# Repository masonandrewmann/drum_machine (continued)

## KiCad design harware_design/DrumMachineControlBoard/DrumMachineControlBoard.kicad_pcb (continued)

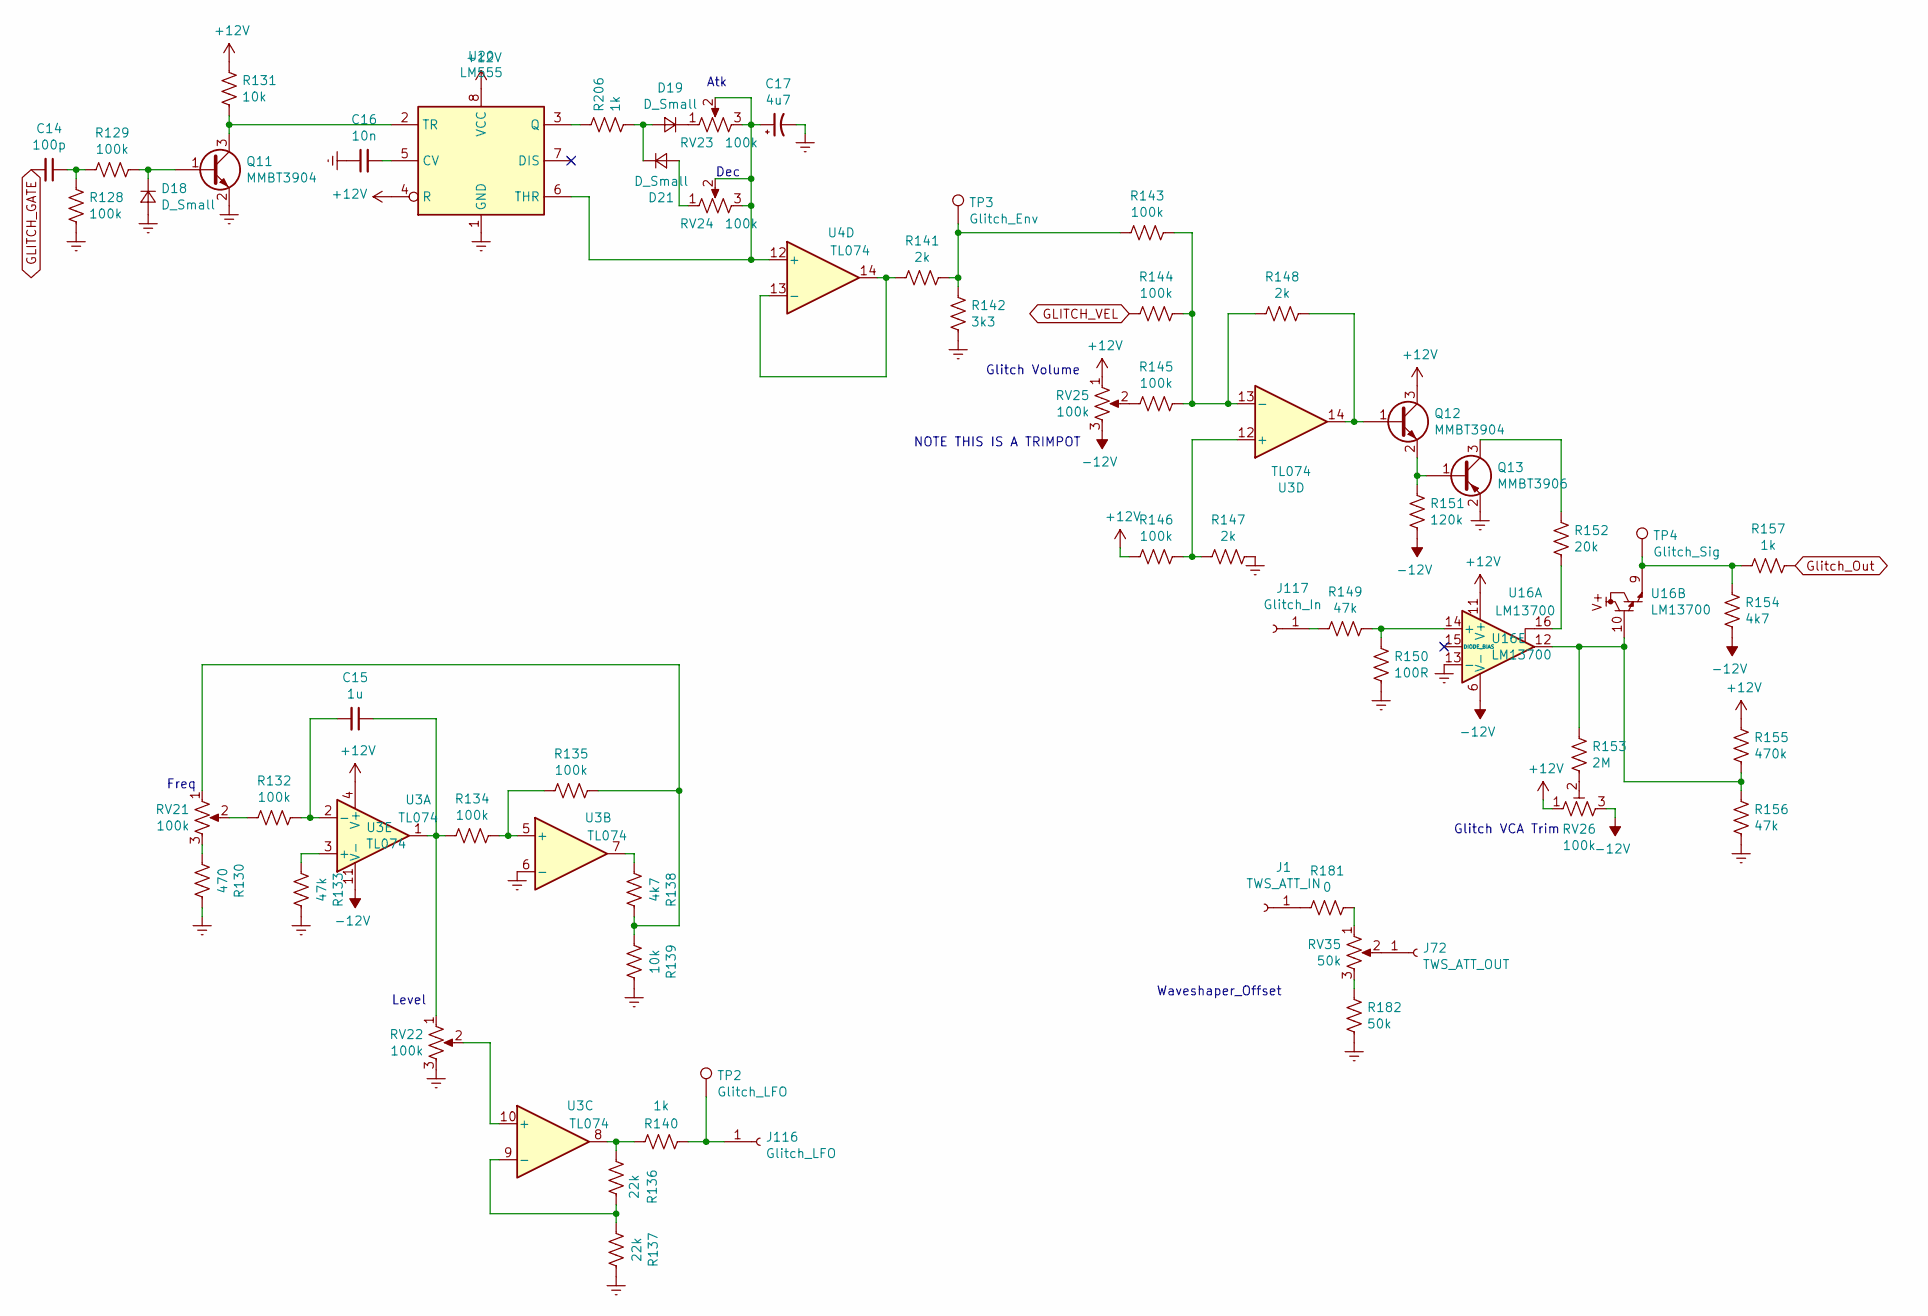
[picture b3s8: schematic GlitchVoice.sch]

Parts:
C14: 100p; C_0603_1608Metric_Pad1.05x0.95mm_HandSolder
C15: 1u; CP_Elec_4x4.5
C16: 10n; C_0603_1608Metric_Pad1.05x0.95mm_HandSolder
C17: 4u7; CP_Elec_4x4.5
D18, D19, D21: D_Small; D_SOD-123
J1: TWS_ATT_IN; SolderWirePad_1x01_Drill1mm
J72: TWS_ATT_OUT; SolderWirePad_1x01_Drill1mm
J116: Glitch_LFO; SolderWirePad_1x01_Drill1mm
J117: Glitch_In; SolderWirePad_1x01_Drill1mm
Q11, Q12: MMBT3904; SOT-23
Q13: MMBT3906; SOT-23
R128, R129, R132, R134, R135, R143, R144, R145, R146: 100k; R_0603_1608Metric_Pad1.05x0.95mm_HandSolder
R130: 470; R_0603_1608Metric_Pad1.05x0.95mm_HandSolder
R131, R139: 10k; R_0603_1608Metric_Pad1.05x0.95mm_HandSolder
R133, R149, R156: 47k; R_0603_1608Metric_Pad1.05x0.95mm_HandSolder
R136, R137: 22k; R_0603_1608Metric_Pad1.05x0.95mm_HandSolder
R138, R154: 4k7; R_0603_1608Metric_Pad1.05x0.95mm_HandSolder
R140, R157, R206: 1k; R_0603_1608Metric_Pad1.05x0.95mm_HandSolder
R141, R147, R148: 2k; R_0603_1608Metric_Pad1.05x0.95mm_HandSolder
R142: 3k3; R_0603_1608Metric_Pad1.05x0.95mm_HandSolder
R150: 100R; R_0603_1608Metric_Pad1.05x0.95mm_HandSolder
R151: 120k; R_0603_1608Metric_Pad1.05x0.95mm_HandSolder
R152: 20k; R_0603_1608Metric_Pad1.05x0.95mm_HandSolder
R153: 2M; R_0603_1608Metric_Pad1.05x0.95mm_HandSolder
R155: 470k; R_0603_1608Metric_Pad1.05x0.95mm_HandSolder
R181: 0; R_0603_1608Metric_Pad1.05x0.95mm_HandSolder
R182: 50k; R_0603_1608Metric_Pad1.05x0.95mm_HandSolder
RV21, RV22, RV23, RV24: 100k; masonsPotentiometer_Alpha_RD901F-40-00D_Single_Vertical
RV25, RV26: 100k; Potentiometer_Runtron_RM-065_Vertical
RV35: 50k; masonsPotentiometer_Alpha_RD901F-40-00D_Single_Vertical
TP2: Glitch_LFO; TestPoint_Loop_D2.50mm_Drill1.0mm
TP3: Glitch_Env; TestPoint_Loop_D2.50mm_Drill1.0mm
TP4: Glitch_Sig; TestPoint_Loop_D2.50mm_Drill1.0mm
U3, U4: TL074; SOIC-14_3.9x8.7mm_P1.27mm
U16: LM13700; SOIC-16_3.9x9.9mm_P1.27mm
U20: LM555; DIP-8_W7.62mm_Socket

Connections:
-12V: R151.2, R154.2, RV25.3, RV26.3, U3.11 (V-), U16.6 (V-); also elsewhere on the board
GLITCH_GATE: C14.2; also elsewhere on the board
GLITCH_VEL: R144.2; also elsewhere on the board
Glitch_Out: R157.1; also elsewhere on the board
unnamed: C14.1, R128.1, R129.2
unnamed: C15.1, R134.2, RV22.1, U3.1
unnamed: C15.2, R132.1, U3.2 (-)
unnamed: C16.2, U20.5 (CV)
unnamed: C17.1, RV23.2, RV23.3, RV24.2, RV24.3, U4.12 (+), U20.6 (THR)
unnamed: D18.1 (K), Q11.1 (B), R129.1
unnamed: D19.1 (K), RV23.1
unnamed: D19.2 (A), D21.1 (K), R206.1
unnamed: D21.2 (A), RV24.1
unnamed: J1.1, R181.2
unnamed: J72.1, RV35.2
unnamed: J116.1, R140.2, TP2.1
unnamed: J117.1, R149.2
unnamed: Q11.3 (C), R131.1, U20.2 (TR)
unnamed: Q12.1 (B), R148.1, U3.14
unnamed: Q12.2 (E), Q13.1 (B), R151.1
unnamed: Q13.3 (C), R152.1
unnamed: R130.2, RV21.3
unnamed: R132.2, RV21.2
unnamed: R133.2, U3.3 (+)
unnamed: R134.1, R135.2, U3.5 (+)
unnamed: R135.1, R138.1, R139.2, RV21.1
unnamed: R136.1, R137.2, U3.9 (-)
unnamed: R136.2, R140.1, U3.8
unnamed: R138.2, U3.7
unnamed: R141.1, U4.13 (-), U4.14
unnamed: R141.2, R142.1, R143.2, TP3.1
unnamed: R143.1, R144.1, R145.1, R148.2, U3.13 (-)
unnamed: R145.2, RV25.2
unnamed: R146.1, R147.2, U3.12 (+)
unnamed: R149.1, R150.1, U16.14 (+)
unnamed: R152.2, U16.16
unnamed: R153.1, R155.2, R156.1, U16.10, U16.12
unnamed: R153.2, RV26.2
unnamed: R154.1, R157.2, TP4.1, U16.9
unnamed: R181.1, RV35.1
unnamed: R182.2, RV35.3
unnamed: R206.2, U20.3 (Q)
unnamed: RV22.2, U3.10 (+)

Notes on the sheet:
Glitch Volume
Glitch VCA Trim
Level
Freq
Atk
Dec
NOTE THIS IS A TRIMPOT
Waveshaper_Offset

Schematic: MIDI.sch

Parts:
D20: 1N4148; D_SOD-123
J11: MIDI IN; DIN5_MIDI
J12: MIDI THRU; DIN5_MIDI
J13: MIDI OUT; DIN5_MIDI
R158, R159, R160, R161: 220; R_0805_2012Metric_Pad1.15x1.40mm_HandSolder
R162: 1k; R_0805_2012Metric_Pad1.15x1.40mm_HandSolder
U21: 74LS04; SOIC-14_3.9x8.7mm_P1.27mm
U22: PC817; DIP-4_W7.62mm

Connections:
+5V: R159.1, R162.2, U21.14 (VCC); also elsewhere on the board
MIDI_IN: R162.1, U21.5, U22.4; also elsewhere on the board
MIDI_OUT: U21.1; also elsewhere on the board
unnamed: D20.1 (K), R160.1, U22.1
unnamed: D20.2 (A), J11.5, U22.2
unnamed: J11.4, R160.2
unnamed 170: J12.4; also elsewhere on the board
unnamed: J12.5, R161.2
unnamed: J13.4, R159.2
unnamed: J13.5, R158.2
unnamed: R158.1, U21.4
unnamed: R161.1, U21.8
unnamed: U21.2, U21.3
unnamed: U21.6, U21.9

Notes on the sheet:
TRIPLE CHECK PINOUT!!!
IDK if any of these circuits work lmao
ALSO LOGIC LEVVELS!
Its not pulling down enough with this resistor
but does when i short it
works better with 220ohm pullup

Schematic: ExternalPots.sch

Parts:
J17: out1W; SolderWirePad_1x01_Drill1mm
J18: env3; SolderWirePad_1x01_Drill1mm
J19: lvl1; SolderWirePad_1x01_Drill1mm
J20: noiseA; SolderWirePad_1x01_Drill1mm
J24: freqA; SolderWirePad_1x01_Drill1mm
J25: env2; SolderWirePad_1x01_Drill1mm
J26: lvl3W; SolderWirePad_1x01_Drill1mm
J27: noise/shimA; SolderWirePad_1x01_Drill1mm
J29: CYNCM_A; SolderWirePad_1x01_Drill1mm
J30: HP_A; SolderWirePad_1x01_Drill1mm
J31: out3; SolderWirePad_1x01_Drill1mm
J32: env1; SolderWirePad_1x01_Drill1mm
J34: shimA; SolderWirePad_1x01_Drill1mm
J35: BP_A; SolderWirePad_1x01_Drill1mm
J36: LP_A; SolderWirePad_1x01_Drill1mm
J37: CYNCM_B; SolderWirePad_1x01_Drill1mm
J38: res1A; SolderWirePad_1x01_Drill1mm
J39: dec1A; SolderWirePad_1x01_Drill1mm
J41: HP_B; SolderWirePad_1x01_Drill1mm
J42: BP_B; SolderWirePad_1x01_Drill1mm
J43: LP_B; SolderWirePad_1x01_Drill1mm
J44: res23A; SolderWirePad_1x01_Drill1mm
J45: dec23A; SolderWirePad_1x01_Drill1mm
J57: Env_1B; SolderWirePad_1x01_Drill1mm
J59: noiseB; SolderWirePad_1x01_Drill1mm
J63: freqB; SolderWirePad_1x01_Drill1mm
J64: Env_2B; SolderWirePad_1x01_Drill1mm
J66: noise/shimB; SolderWirePad_1x01_Drill1mm
J71: Env_3B; SolderWirePad_1x01_Drill1mm
J73: shimB; SolderWirePad_1x01_Drill1mm
J77: res1B; SolderWirePad_1x01_Drill1mm
J78: dec1B; SolderWirePad_1x01_Drill1mm
J83: res23B; SolderWirePad_1x01_Drill1mm
J84: dec23B; SolderWirePad_1x01_Drill1mm
J92: atk1W; SolderWirePad_1x01_Drill1mm
J93: tune; SolderWirePad_1x01_Drill1mm
J94: dist1W; SolderWirePad_1x01_Drill1mm
J95: snap1; SolderWirePad_1x01_Drill1mm
J96: Tone1; SolderWirePad_1x01_Drill1mm
J101: Tone2; SolderWirePad_1x01_Drill1mm
J102: atk3; SolderWirePad_1x01_Drill1mm
J104: dist3; SolderWirePad_1x01_Drill1mm
J105: snap3w; SolderWirePad_1x01_Drill1mm
J106: Tone3; SolderWirePad_1x01_Drill1mm
J107: tune3; SolderWirePad_1x01_Drill1mm
J108: depth1; SolderWirePad_1x01_Drill1mm
J109: dec1w; SolderWirePad_1x01_Drill1mm
J110: tunew; SolderWirePad_1x01_Drill1mm
J111: depthw; SolderWirePad_1x01_Drill1mm
J113: tune1; SolderWirePad_1x01_Drill1mm
J114: depth3; SolderWirePad_1x01_Drill1mm
J115: dec3; SolderWirePad_1x01_Drill1mm
J146: AuxPot1; SolderWirePad_1x01_Drill1mm
J147, J148: AuxPot2; SolderWirePad_1x01_Drill1mm
J149: AuxPot1A; SolderWirePad_1x01_Drill1mm
J150, J151: AuxPot2A; SolderWirePad_1x01_Drill1mm
RV8, RV30, RV33, RV40, RV49, RV52, RV54, RV55, RV57, RV66: 100k; masonsPotentiometer_Alpha_RD901F-40-00D_Single_Vertical
RV14: 50k; masonsPotentiometer_Alpha_RD901F-40-00D_Single_Vertical
RV31, RV50: 25k; masonsPotentiometer_Alpha_RD901F-40-00D_Single_Vertical
RV39, RV56: 1k; masonsPotentiometer_Alpha_RD901F-40-00D_Single_Vertical
RV59: 470; Amphenol_Trimpot
RV60, RV61, RV62, RV64: 10k; masonsPotentiometer_Alpha_RD901F-40-00D_Single_Vertical
RV63: 500k; masonsPotentiometer_Alpha_RD901F-40-00D_Single_Vertical
RV65: 1M; masonsPotentiometer_Alpha_RD901F-40-00D_Single_Vertical
U26: SP3TCYNA; two-pole-switch
U27: SP3TCYNB; two-pole-switch

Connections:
-12V: RV30.1, RV49.1; also elsewhere on the board
unnamed: J17.1, RV14.1, RV14.2
unnamed: J18.1, RV31.1
unnamed: J19.1, RV8.1
unnamed: J20.1, RV33.1
unnamed: J24.1, RV30.2
unnamed: J25.1, RV31.2
unnamed: J26.1, RV8.2, RV8.3
unnamed: J27.1, RV33.2
unnamed: J29.1, U26.2
unnamed: J30.1, U26.1
unnamed: J31.1, RV14.3
unnamed: J32.1, RV31.3
unnamed: J34.1, RV33.3
unnamed: J35.1, U26.4
unnamed: J36.1, U26.6
unnamed: J37.1, U27.2
unnamed: J38.1, RV39.1
unnamed: J39.1, RV40.1
unnamed: J41.1, U27.1
unnamed: J42.1, U27.4
unnamed: J43.1, U27.6
unnamed: J44.1, RV39.2, RV39.3
unnamed: J45.1, RV40.2, RV40.3
unnamed: J57.1, RV50.1
unnamed: J59.1, RV52.1
unnamed: J63.1, RV49.2
unnamed: J64.1, RV50.2
unnamed: J66.1, RV52.2
unnamed: J71.1, RV50.3
unnamed: J73.1, RV52.3
unnamed: J77.1, RV56.1
unnamed: J78.1, RV57.1
unnamed: J83.1, RV56.2, RV56.3
unnamed: J84.1, RV57.2, RV57.3
unnamed: J92.1, RV59.1, RV59.2
unnamed: J93.1, RV60.1
unnamed: J94.1, RV61.1, RV61.2
unnamed: J95.1, RV62.1
unnamed: J96.1, RV63.1
unnamed: J101.1, RV63.2
unnamed: J102.1, RV59.3
unnamed: J104.1, RV61.3
unnamed: J105.1, RV62.2, RV62.3
unnamed: J106.1, RV63.3
unnamed: J107.1, RV64.1
unnamed: J108.1, RV65.1
unnamed: J109.1, RV66.1, RV66.2
unnamed: J110.1, RV64.2
unnamed: J111.1, RV65.2
unnamed: J113.1, RV64.3
unnamed: J114.1, RV65.3
unnamed: J115.1, RV66.3
unnamed: J146.1, RV54.1
unnamed: J147.1, RV54.2
unnamed: J148.1, RV54.3
unnamed: J149.1, RV55.1
unnamed: J150.1, RV55.2
unnamed: J151.1, RV55.3
unnamed: U26.3, U26.5
unnamed: U27.3, U27.5

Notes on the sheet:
VCF_FreqA
VCF_ResA
EnvA
DecA
Shim/NoiseA
CYNARE A
VCF_FreqB
VCF_ResB
EnvB
DecB
Shim/NoiseB
CYNARE B
Atk
Dec
TuneDep
TuneDec
Dist
Bass Drum
Snap
Tune
Tone
Snare
level

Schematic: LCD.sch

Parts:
J145: Conn_01x08_Female; PinSocket_1x08_P2.54mm_Vertical
R177: 220; R_0603_1608Metric_Pad1.05x0.95mm_HandSolder
U24: Nokia5110; Nokia5110Breakout

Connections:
+3V3: J145.3, R177.2, U24.3 (VCC); also elsewhere on the board
LCD_CS: J145.7, U24.7 (CE); also elsewhere on the board
LCD_DC: J145.6, U24.6 (DC); also elsewhere on the board
LCD_RST: J145.8, U24.8 (RST); also elsewhere on the board
MEM_MOSI: J145.5, U24.5 (DIN)
MEM_SCK: J145.4, U24.4 (CLK); also elsewhere on the board
unnamed: J145.2, R177.1, U24.2 (LIGHT)

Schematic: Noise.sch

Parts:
C30: 1u; CP_Elec_4x4.5
C36: 100n; C_0603_1608Metric_Pad1.05x0.95mm_HandSolder
C37: 10u; CP_Elec_5x5.3
J14: BD_Noise; SolderWirePad_1x01_Drill1mm
J15: Snare_Noise; SolderWirePad_1x01_Drill1mm
Q23: 2N3904; TO-92_Inline_Wide
R194: 2M; R_0603_1608Metric_Pad1.05x0.95mm_HandSolder
R195: 100k; R_0603_1608Metric_Pad1.05x0.95mm_HandSolder
R196: 4M7; R_0603_1608Metric_Pad1.05x0.95mm_HandSolder
R197, R198: 10k; R_0603_1608Metric_Pad1.05x0.95mm_HandSolder
R199, R200: 2M; R_Axial_DIN0207_L6.3mm_D2.5mm_P7.62mm_Horizontal
R207, R208: 470k; R_0603_1608Metric_Pad1.05x0.95mm_HandSolder
RV11, RV15: 100k; Potentiometer_Runtron_RM-065_Vertical
U29: TL074; SOIC-14_3.9x8.7mm_P1.27mm

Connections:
-12V: Q23.2 (B), U29.11 (V-); also elsewhere on the board
unnamed: C30.1, R207.1, R208.1
unnamed: C36.1, Q23.1 (E), R208.2
unnamed: C36.2, R194.1, U29.3 (+)
unnamed: C37.1, R195.1
unnamed: J14.1, R200.1, U29.7
unnamed: J15.1, R199.1, U29.8
unnamed: R195.2, R196.2, U29.2 (-)
unnamed: R196.1, RV11.1, RV15.1, U29.1
unnamed: R197.1, R200.2, U29.6 (-)
unnamed: R197.2, RV11.2
unnamed: R198.1, R199.2, U29.9 (-)
unnamed: R198.2, RV15.2

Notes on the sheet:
BD_Noise_LVL
Snare_Noise_LVL

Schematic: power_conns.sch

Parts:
J47: PWR_CONN; JST_XH_B5B-XH-A_1x05_P2.50mm_Vertical
J48: SNARE_PWR; JST_XH_B3B-XH-A_1x03_P2.50mm_Vertical
J49: BD_PWR; JST_XH_B3B-XH-A_1x03_P2.50mm_Vertical
J50: CYN1_PWR; JST_XH_B3B-XH-A_1x03_P2.50mm_Vertical
J51: CYN2_PWR; JST_XH_B3B-XH-A_1x03_P2.50mm_Vertical
J52: TWS_PWR; JST_XH_B3B-XH-A_1x03_P2.50mm_Vertical

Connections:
+5V: J47.2; also elsewhere on the board
-12V: J47.5, J48.3, J49.3, J50.3, J51.3, J52.3; also elsewhere on the board

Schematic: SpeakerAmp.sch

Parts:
C24: 10u; CP_Elec_4x4.5
C25: 100n; C_0805_2012Metric_Pad1.15x1.40mm_HandSolder
J16: spk_Conn; JST_XH_B2B-XH-A_1x02_P2.50mm_Vertical
R180: 10k; R_0805_2012Metric_Pad1.15x1.40mm_HandSolder
RV16: 1M; Potentiometer_Runtron_RM-065_Vertical
SW33: SW_SPDT; one-pole-switch
U28: NJM2073S; SIP-9_21.54x3mm_P2.54mm

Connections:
unnamed: C24.1, U28.9 (A-)
unnamed: C24.2, C25.1, U28.6 (B-)
unnamed: J16.1, U28.4 (B_Out)
unnamed: J16.2, U28.2 (A_Out)
unnamed: R180.2, RV16.3, U28.8 (A+)
unnamed: RV16.1, RV16.2, SW33.2 (B)

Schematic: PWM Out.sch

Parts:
C18, C19, C20, C21, C22, C23: 100n; C_0805_2012Metric_Pad1.15x1.40mm_HandSolder
J124: Kick_Vel; SolderWirePad_1x01_Drill1mm
J125: Snare_Vel; SolderWirePad_1x01_Drill1mm
J126: CYN1_Vel; SolderWirePad_1x01_Drill1mm
J127: CYN2_Vel; SolderWirePad_1x01_Drill1mm
R163, R164, R165, R166, R171, R172: 10k; R_0805_2012Metric_Pad1.15x1.40mm_HandSolder
R167, R168, R169, R170, R173, R174: 4k7; R_0805_2012Metric_Pad1.15x1.40mm_HandSolder
RV67, RV68, RV69, RV70, RV71, RV72: 10k; Potentiometer_Runtron_RM-065_Vertical
U1: TL074; SOIC-14_3.9x8.7mm_P1.27mm
U2: TL072; SOIC-8_3.9x4.9mm_P1.27mm

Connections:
CYN1_PWM: R165.2; also elsewhere on the board
CYN2_PWM: R166.2; also elsewhere on the board
FILTER_CUTOFF: RV72.2, RV72.3, U2.7; also elsewhere on the board
FILTER_PWM: R171.2; also elsewhere on the board
GLITCH_PWM: R172.2; also elsewhere on the board
GLITCH_VEL: RV71.2, RV71.3, U2.1; also elsewhere on the board
KICK_PWM: R163.2; also elsewhere on the board
unnamed: C18.2, R163.1, U1.3 (+)
unnamed: C19.2, R164.1, U1.5 (+)
unnamed: C20.2, R165.1, U1.10 (+)
unnamed: C21.2, R166.1, U1.12 (+)
unnamed: C22.2, R171.1, U2.5 (+)
unnamed: C23.2, R172.1, U2.3 (+)
unnamed: J124.1, RV67.2, RV67.3, U1.1
unnamed: J125.1, RV68.2, RV68.3, U1.7
unnamed: J126.1, RV69.2, RV69.3, U1.8
unnamed: J127.1, RV70.2, RV70.3, U1.14
unnamed: R167.2, RV67.1, U1.2 (-)
unnamed: R168.2, RV68.1, U1.6 (-)
unnamed: R169.2, RV69.1, U1.9 (-)
unnamed: R170.2, RV70.1, U1.13 (-)
unnamed: R173.2, RV71.1, U2.2 (-)
unnamed: R174.2, RV72.1, U2.6 (-)
SNARE_PWM: R164.2; also elsewhere on the board

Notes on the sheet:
PWM Freq 448200
PWM Resolution 10bits
CHECK IF ITS OKAY TO USE GND AAND NOT -12V FOR VSS!!!!!

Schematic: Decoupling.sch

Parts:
C26, C27, C28, C29, C31, C32, C33, C40, C41, C42, C43, C44, C45, C46, C47, C48, C49, C50, C51, C52, C53, C54, C55, C56, C57, C58, C59, C60, C61, C62, C69, C70: 100n; C_0603_1608Metric_Pad1.05x0.95mm_HandSolder
C63, C64: 10u; CP_Elec_5x5.3

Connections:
+3V3: C40.1, C41.1, C42.1, C43.1, C44.1, C45.1, C46.1; also elsewhere on the board
+5V: C26.1, C27.1, C28.1, C29.1, C31.1, C32.1, C33.1; also elsewhere on the board
-12V: C48.2, C50.2, C52.2, C56.2, C58.2, C60.2, C64.2; also elsewhere on the board

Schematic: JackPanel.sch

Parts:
J74: Barrel_Jack; BarrelJack_Horizontal
J75: MIX_LINE; NMJ4HFD2
J76: MIX_HEADPHONE; NRJ6HH-AU
J79: Conn_01x03_Male; JST_XH_B3B-XH-A_1x03_P2.50mm_Vertical
J80: CYNA1-1; SolderWirePad_1x01_Drill1mm
J81: CYNA2-1; SolderWirePad_1x01_Drill1mm
J82: CYNA3-1; SolderWirePad_1x01_Drill1mm
J85: CYNA4-1; SolderWirePad_1x01_Drill1mm
J86: CYNA5-1; SolderWirePad_1x01_Drill1mm
J87: CYNA6-1; SolderWirePad_1x01_Drill1mm
J88: CYNA1-W3; SolderWirePad_1x01_Drill1mm
J89: CYNA2-W3; SolderWirePad_1x01_Drill1mm
J90: CYNA3-W3; SolderWirePad_1x01_Drill1mm
J91: CYNA4-W3; SolderWirePad_1x01_Drill1mm
J97: CYNA5-W3; SolderWirePad_1x01_Drill1mm
J98: CYNA6-W3; SolderWirePad_1x01_Drill1mm
J99: CYNB1-1; SolderWirePad_1x01_Drill1mm
J100: CYNB2-1; SolderWirePad_1x01_Drill1mm
J103: CYNB3-1; SolderWirePad_1x01_Drill1mm
J112: CYNB4-1; SolderWirePad_1x01_Drill1mm
J128: CYNB5-1; SolderWirePad_1x01_Drill1mm
J129: CYNB6-1; SolderWirePad_1x01_Drill1mm
J130: CYNB1-W3; SolderWirePad_1x01_Drill1mm
J131: CYNB2-W3; SolderWirePad_1x01_Drill1mm
J132: CYNB3-W3; SolderWirePad_1x01_Drill1mm
J141: CYNB4-W3; SolderWirePad_1x01_Drill1mm
J143: CYNB5-W3; SolderWirePad_1x01_Drill1mm
J144: CYNB6-W3; SolderWirePad_1x01_Drill1mm
RV36, RV37, RV38, RV41, RV42, RV43, RV44, RV45, RV46, RV47, RV48, RV51: 500k; masonsPotentiometer_Alpha_RD901F-40-00D_Single_Vertical
RV53: 10k; Potentiometer_Runtron_RM-065_Vertical
U33: TL072; SOIC-8_3.9x4.9mm_P1.27mm

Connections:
unnamed: J74.1, J79.3
unnamed: J74.2, J79.1, J79.2
unnamed: J80.1, RV36.1
unnamed: J81.1, RV37.1
unnamed: J82.1, RV38.1
unnamed: J85.1, RV41.1
unnamed: J86.1, RV42.1
unnamed: J87.1, RV43.1
unnamed: J88.1, RV36.2, RV36.3
unnamed: J89.1, RV37.2, RV37.3
unnamed: J90.1, RV38.2, RV38.3
unnamed: J91.1, RV41.2, RV41.3
unnamed: J97.1, RV42.2, RV42.3
unnamed: J98.1, RV43.2, RV43.3
unnamed: J99.1, RV44.1
unnamed: J100.1, RV45.1
unnamed: J103.1, RV46.1
unnamed: J112.1, RV47.1
unnamed: J128.1, RV48.1
unnamed: J129.1, RV51.1
unnamed: J130.1, RV44.2, RV44.3
unnamed: J131.1, RV45.2, RV45.3
unnamed: J132.1, RV46.2, RV46.3
unnamed: J141.1, RV47.2, RV47.3
unnamed: J143.1, RV48.2, RV48.3
unnamed: J144.1, RV51.2, RV51.3

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
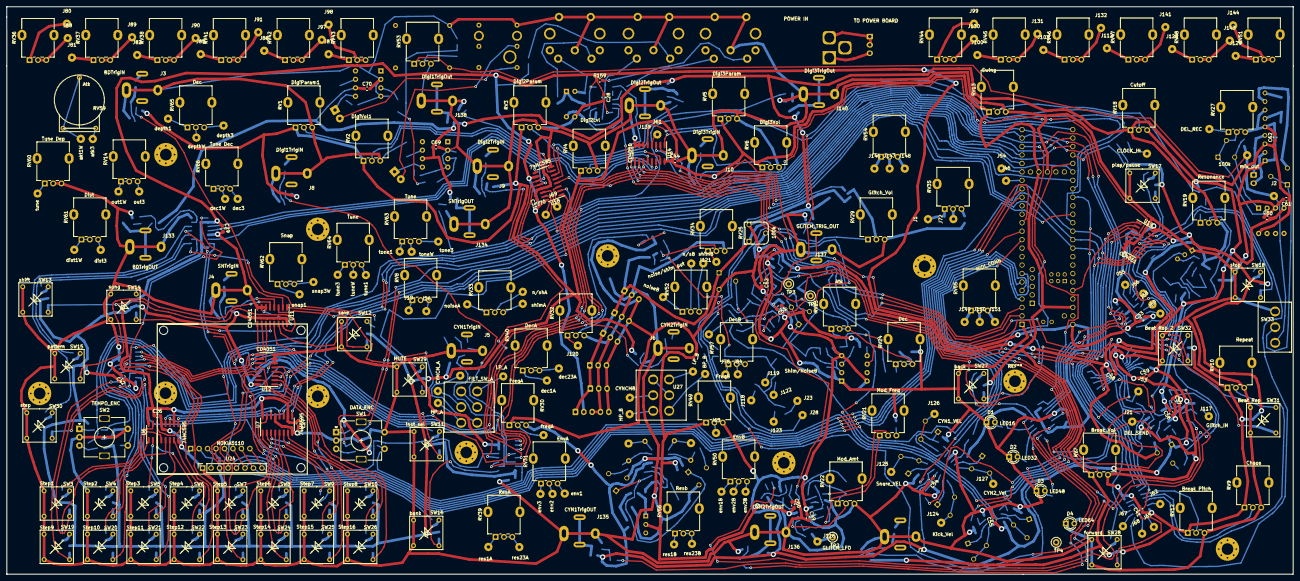
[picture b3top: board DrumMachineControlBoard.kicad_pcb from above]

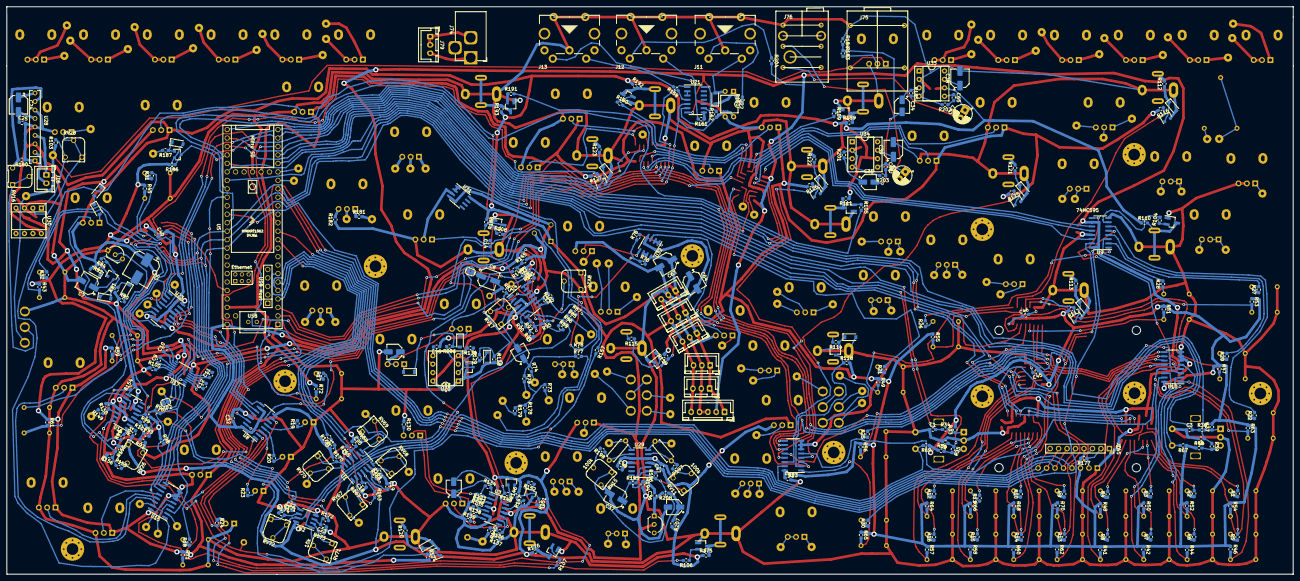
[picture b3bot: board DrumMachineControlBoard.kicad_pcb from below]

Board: 2 copper layers, 385.8 x 170.2 mm, 616 parts (348 on the bottom side), 459 nets.

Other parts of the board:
C34, C35: 1u; CP_Elec_4x4.5
C38, C39: 10u; CP_Elec_5x5.3
C65, C66: 47n; C_0603_1608Metric_Pad1.05x0.95mm_HandSolder
C67, C68: 220u; CP_Radial_D5.0mm_P2.0mm_Bigger_Holes
D1: RED_16; LED_D3.0mm
D2: RED_32; LED_D3.0mm
D3: RED_48; LED_D3.0mm
D4: RED_64; LED_D3.0mm
J55: SR_AUX_1; SolderWirePad_1x01_Drill1mm
J56: SR_AUX_2; SolderWirePad_1x01_Drill1mm
J58: SR_AUX_3; SolderWirePad_1x01_Drill1mm
J60: SR_AUX_4; SolderWirePad_1x01_Drill1mm
R1, R2, R3, R4, R5, R6, R7, R8, R9, R10, R11, R12, R13, R14, R15, R16, R17, R18, R21, R22, R25, R26, R27, R28, R29, R30, R31, R32, R204: 220; R_0603_1608Metric_Pad1.05x0.95mm_HandSolder
R19, R20, R23, R24: 1k; R_0603_1608Metric_Pad1.05x0.95mm_HandSolder
R183: 470k; R_0603_1608Metric_Pad1.05x0.95mm_HandSolder
R184: 20k; R_0603_1608Metric_Pad1.05x0.95mm_HandSolder
R185, R201: 10k; R_0603_1608Metric_Pad1.05x0.95mm_HandSolder
R202, R203: 10; R_0603_1608Metric_Pad1.05x0.95mm_HandSolder
U6, U7, U8, U9, U23: 74HC595; SOIC-16_3.9x9.9mm_P1.27mm
U34: LM386; DIP-8_W7.62mm_Socket

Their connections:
+5V: R204.2, U6.10, U6.16, U7.10, U7.16, U8.10, U8.16, U9.10, U9.16, U23.10, U23.16; also elsewhere on the board
BD_TRIG_OUT: U9.7; also elsewhere on the board
CYN_TRIG_1: U8.15; also elsewhere on the board
CYN_TRIG_2: U8.7; also elsewhere on the board
L1A: R1.1; also elsewhere on the board
L2A: R2.1; also elsewhere on the board
L3A: R3.1; also elsewhere on the board
L4A: R4.1; also elsewhere on the board
L5A: R9.1; also elsewhere on the board
L6A: R10.1; also elsewhere on the board
L7A: R11.1; also elsewhere on the board
L8A: R12.1; also elsewhere on the board
L9A: R5.1; also elsewhere on the board
L10A: R6.1; also elsewhere on the board
L11A: R7.1; also elsewhere on the board
L12A: R8.1; also elsewhere on the board
L13A: R13.1; also elsewhere on the board
L14A: R14.1; also elsewhere on the board
L15A: R15.1; also elsewhere on the board
L16A: R16.1; also elsewhere on the board
LED_CLK: U6.11, U7.11, U8.11, U9.11, U23.11; also elsewhere on the board
LED_LATCH: U6.12, U7.12, U8.12, U9.12, U23.12; also elsewhere on the board
LED_SERIAL: U8.14; also elsewhere on the board
LED_SR_OUT: U23.9; also elsewhere on the board
L_back: R17.1; also elsewhere on the board
L_bank: R30.1; also elsewhere on the board
L_forwards: R18.1; also elsewhere on the board
L_inst_sel: R25.1; also elsewhere on the board
L_mute: R21.1; also elsewhere on the board
L_pattern: R29.1; also elsewhere on the board
L_playpause: R31.1; also elsewhere on the board
L_save: R26.1; also elsewhere on the board
L_shift: R27.1; also elsewhere on the board
L_song: R28.1; also elsewhere on the board
L_step: R22.1; also elsewhere on the board
L_stop: R32.1; also elsewhere on the board
MUTE_LED: R21.2; also elsewhere on the board
unnamed: C34.2, C35.2, R183.1, R184.2
unnamed: C35.1, R201.1, U34.3
unnamed: C39.1, U34.7
unnamed: C65.2, R202.1
unnamed: C66.1, C68.1, U34.5
unnamed: C66.2, R203.1
unnamed: D1.2, R19.1
unnamed: D2.2, R20.1
unnamed: D3.2, R23.1
unnamed: D4.2, R24.1
unnamed 170: R204.1; also elsewhere on the board
unnamed: J55.1, U23.4
unnamed: J56.1, U23.5
unnamed: J58.1, U23.6
unnamed: J60.1, U23.7
unnamed: R1.2, U6.15
unnamed: R2.2, U6.1
unnamed: R3.2, U6.2
unnamed: R4.2, U6.3
unnamed: R5.2, U6.4
unnamed: R6.2, U6.5
unnamed: R7.2, U6.6
unnamed: R8.2, U6.7
unnamed: R9.2, U7.15
unnamed: R10.2, U7.1
unnamed: R11.2, U7.2
unnamed: R12.2, U7.3
unnamed: R13.2, U7.4
unnamed: R14.2, U7.5
unnamed: R15.2, U7.6
unnamed: R16.2, U7.7
unnamed: R17.2, U8.6
unnamed: R18.2, U8.1
unnamed: R19.2, U8.5
unnamed: R20.2, U8.4
unnamed: R22.2, U9.6
unnamed: R23.2, U8.3
unnamed: R24.2, U8.2
unnamed: R25.2, U9.15
unnamed: R26.2, U9.1
unnamed: R27.2, U9.2
unnamed: R28.2, U9.3
unnamed: R29.2, U9.4
unnamed: R30.2, U9.5
unnamed: R31.2, U23.1
unnamed: R32.2, U23.2
unnamed: U6.9, U7.14
unnamed: U6.14, U9.9
unnamed: U8.9, U23.14
SR_U18_OUT: U9.14; also elsewhere on the board
beat_rep: U23.15; also elsewhere on the board
beat_rep_2: U23.3; also elsewhere on the board

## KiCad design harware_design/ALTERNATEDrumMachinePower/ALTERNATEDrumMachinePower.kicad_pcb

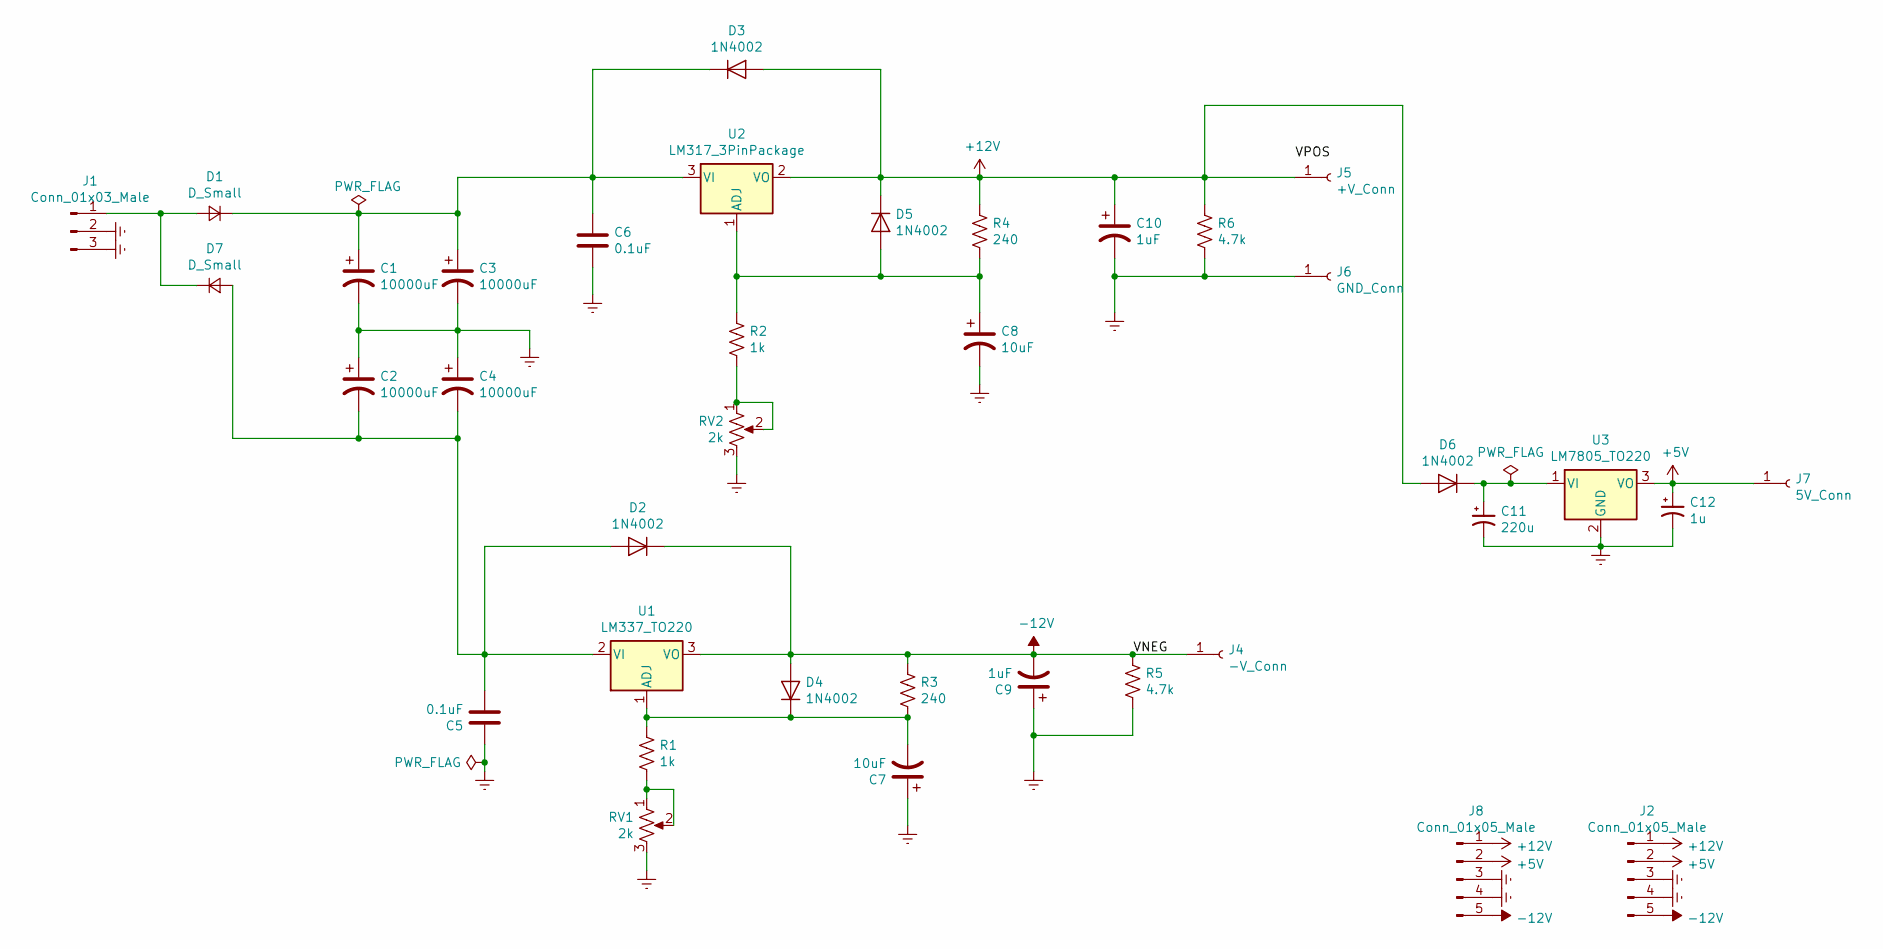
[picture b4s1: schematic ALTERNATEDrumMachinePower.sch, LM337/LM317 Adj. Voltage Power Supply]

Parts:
C1, C2, C3, C4: 10000uF; CP_Radial_D30.0mm_P10.00mm_SnapIn
C5, C6: 0.1uF; C_Rect_L7.0mm_W2.5mm_P5.00mm
C7, C8: 10uF; CP_Radial_D5.0mm_P2.0mm_Bigger_Holes
C9, C10: 1uF; CP_Radial_D5.0mm_P2.0mm_Bigger_Holes
C11: 220u; CP_Radial_D5.0mm_P2.0mm_Bigger_Holes
C12: 1u; CP_Radial_D5.0mm_P2.0mm_Bigger_Holes
D1, D7: D_Small; D_DO-41_SOD81_P10.16mm_Horizontal
D2, D3, D4, D5, D6: 1N4002; D_DO-41_SOD81_P10.16mm_Horizontal
J1: Conn_01x03_Male; JST_XH_B3B-XH-A_1x03_P2.50mm_Vertical
J2, J8: Conn_01x05_Male; JST_XH_B5B-XH-A_1x05_P2.50mm_Vertical
J4: -V_Conn; Pin_D1.1mm_L10.2mm_W3.5mm_Flat
J5: +V_Conn; Pin_D1.1mm_L10.2mm_W3.5mm_Flat
J6: GND_Conn; Pin_D1.1mm_L10.2mm_W3.5mm_Flat
J7: 5V_Conn; Pin_D1.1mm_L10.2mm_W3.5mm_Flat
R1, R2: 1k; R_Axial_DIN0207_L6.3mm_D2.5mm_P7.62mm_Horizontal
R3, R4: 240; R_Axial_DIN0207_L6.3mm_D2.5mm_P7.62mm_Horizontal
R5, R6: 4.7k; R_Axial_DIN0207_L6.3mm_D2.5mm_P7.62mm_Horizontal
RV1, RV2: 2k; Potentiometer_Runtron_RM-065_Vertical
U1: LM337_TO220; TO-220-3_Vertical
U2: LM317_3PinPackage; TO-220-3_Vertical
U3: LM7805_TO220; TO-220-3_Vertical

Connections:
+5V: C12.1, J2.2, J7.1, J8.2, U3.3 (VO)
+12V: C10.1, D3.2 (A), D5.1 (K), D6.2 (A), J2.1, J5.1, J8.1, R4.1, R6.1, U2.2 (VO)
-12V: C9.2, D2.1 (K), D4.2 (A), J2.5, J4.1, J8.5, R3.1, R5.1, U1.3 (VO)
Earth: C1.2, C2.1, C3.2, C4.1, C5.1, C6.2, C7.1, C8.2, C9.1, C10.2, C11.2, C12.2, J1.2, J1.3, J2.3, J2.4, J6.1, J8.3, J8.4, R5.2, R6.2, RV1.3, RV2.3, U3.2 (GND)
unnamed: C1.1, C3.1, C6.1, D1.1 (K), D3.1 (K), U2.3 (VI)
unnamed: C2.2, C4.2, C5.2, D2.2 (A), D7.2 (A), U1.2 (VI)
unnamed: C7.2, D4.1 (K), R1.1, R3.2, U1.1 (ADJ)
unnamed: C8.1, D5.2 (A), R2.1, R4.2, U2.1 (ADJ)
unnamed: C11.1, D6.1 (K), U3.1 (VI)
unnamed: D1.2 (A), D7.1 (K), J1.1
unnamed: R1.2, RV1.1, RV1.2
unnamed: R2.2, RV2.1, RV2.2

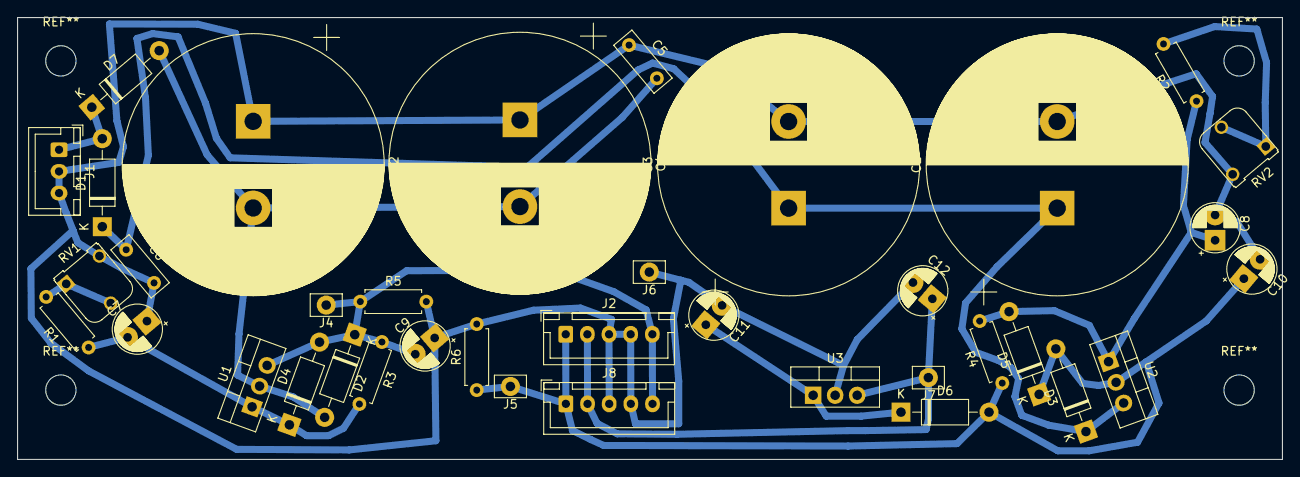
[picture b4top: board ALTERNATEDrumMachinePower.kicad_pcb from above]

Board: 2 copper layers, 146.0 x 51.0 mm, 37 parts (0 on the bottom side), 12 nets.

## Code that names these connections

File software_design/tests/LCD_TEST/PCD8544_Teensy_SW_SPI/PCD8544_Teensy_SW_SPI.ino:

#include <Arduino.h>
#include <U8g2lib.h>
#include <SPI.h>

#define LCD_SCK 13
#define LCD_MOSI 11
#define LCD_MISO 12
#define LCD_DC 25
#define LCD_CS 10
#define LCD_RST 24


// End of constructor list

U8G2_PCD8544_84X48_F_4W_HW_SPI u8g2(U8G2_R2, LCD_CS, LCD_DC, LCD_RST);


//u8g2_t u8g2;
 int xx;

void setup(void) {
u8g2.begin();
 xx = 10;
//SPI.begin();
// SPI.setClockDivider(128);
}

void loop(void) {
  u8g2.clearBuffer();          // clear the internal memory
  u8g2.setFont(u8g2_font_ncenB08_tr); // choose a suitable font
  u8g2.drawStr(0,11,"Hello Worldo!");  // write something to the internal memory
  u8g2.drawStr(20,30," <3");  // write something to the internal memory
  u8g2.sendBuffer();          // transfer internal memory to the display
  delay(1000);   
}

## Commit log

2023-01-11 big update, basic drum sequencing is working here
2023-01-13 basics working
2023-01-25 pattern saving works
2023-01-31 before trying QSPI sample playback
2023-02-01 samples playing from SPI RAM
2023-02-01 some reorganizing
2023-02-01 cleaned up pattern chaining
2023-02-02 sample voice parameters are saved to SD per pattern
2023-02-02 fixed pattern save bug
2023-02-02 sd patterns updated
2023-02-03 swing implemented
2023-02-03 tempo display added
2023-02-14 forgot to commit last week
2023-02-14 added two more kits and basic kit selection, tempo gets saved per pattern too
2023-02-14 press tempo encoder to view tempo
2023-02-15 a bunch of formatting and commenting plus some minor changes
2023-02-15 some more commenting and cleanup
2023-02-15 cleaned up kit switching and fixed some silly little glitches
2023-02-16 songs implemented plus some menu stuff cleaned up
2023-02-16 added two chord sample voices
2023-02-17 added melody voice
2023-02-17 swapped some samples and expanded pattern object
2023-02-17 implemented 5 more sample note voices
2023-02-17 fresh morning commit
2023-02-17 first attempt at long patterns, its not workinggit add . memory problems i think
2023-02-17 having git probklems
2023-02-17 more git probs
2023-02-17 hopefully restoring
2023-02-17 fixed some silly memory usage stuff, modified start mem in flashloader.h
2023-02-17 forgor to commit
2023-02-17 long pattern object updated, not implemented in main code yet
2023-02-17 implemented long patterns and added a silly bitcrusher to master
2023-02-17 automated pattern recall strings
2023-02-17 automated pattern save strings
2023-02-18 up to date but theres some crazy distortion going on with the samples
2023-02-19 bug fixes
2023-02-20 started adding midi, clock kinda works
2023-02-21 fixed sprintf omtimizer error and added copy paste and clear to patterns
2023-02-23 updated SD backup
2023-02-28 added pattern and song naming
